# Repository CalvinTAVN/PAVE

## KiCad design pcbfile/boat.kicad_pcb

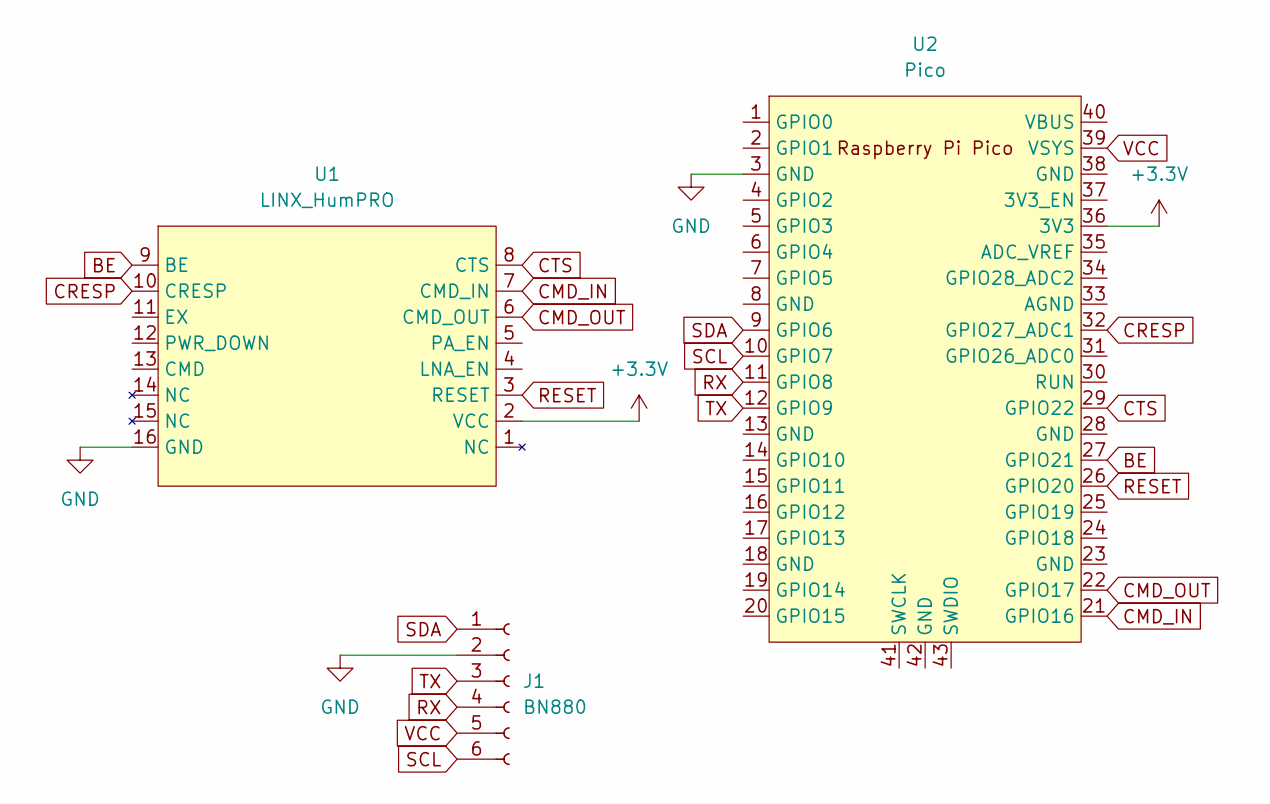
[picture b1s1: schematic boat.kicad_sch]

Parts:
J1: BN880; PinSocket_1x06_P2.54mm_Vertical
U1: LINX_HumPRO; Linx_HumPRO
U2: Pico; RPi_Pico_SMD_TH

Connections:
+3.3V: U1.2 (VCC), U2.36 (3V3)
BE: U1.9 (BE), U2.27 (GPIO21)
CMD_IN: U1.7 (CMD_IN), U2.21 (GPIO16)
CMD_OUT: U1.6 (CMD_OUT), U2.22 (GPIO17)
CRESP: U1.10 (CRESP), U2.32 (GPIO27_ADC1)
CTS: U1.8 (CTS), U2.29 (GPIO22)
GND: J1.2, U1.16 (GND), U2.3 (GND)
RESET: U1.3 (RESET), U2.26 (GPIO20)
RX: J1.4, U2.11 (GPIO8)
SCL: J1.6, U2.10 (GPIO7)
SDA: J1.1, U2.9 (GPIO6)
TX: J1.3, U2.12 (GPIO9)
VCC: J1.5, U2.39 (VSYS)

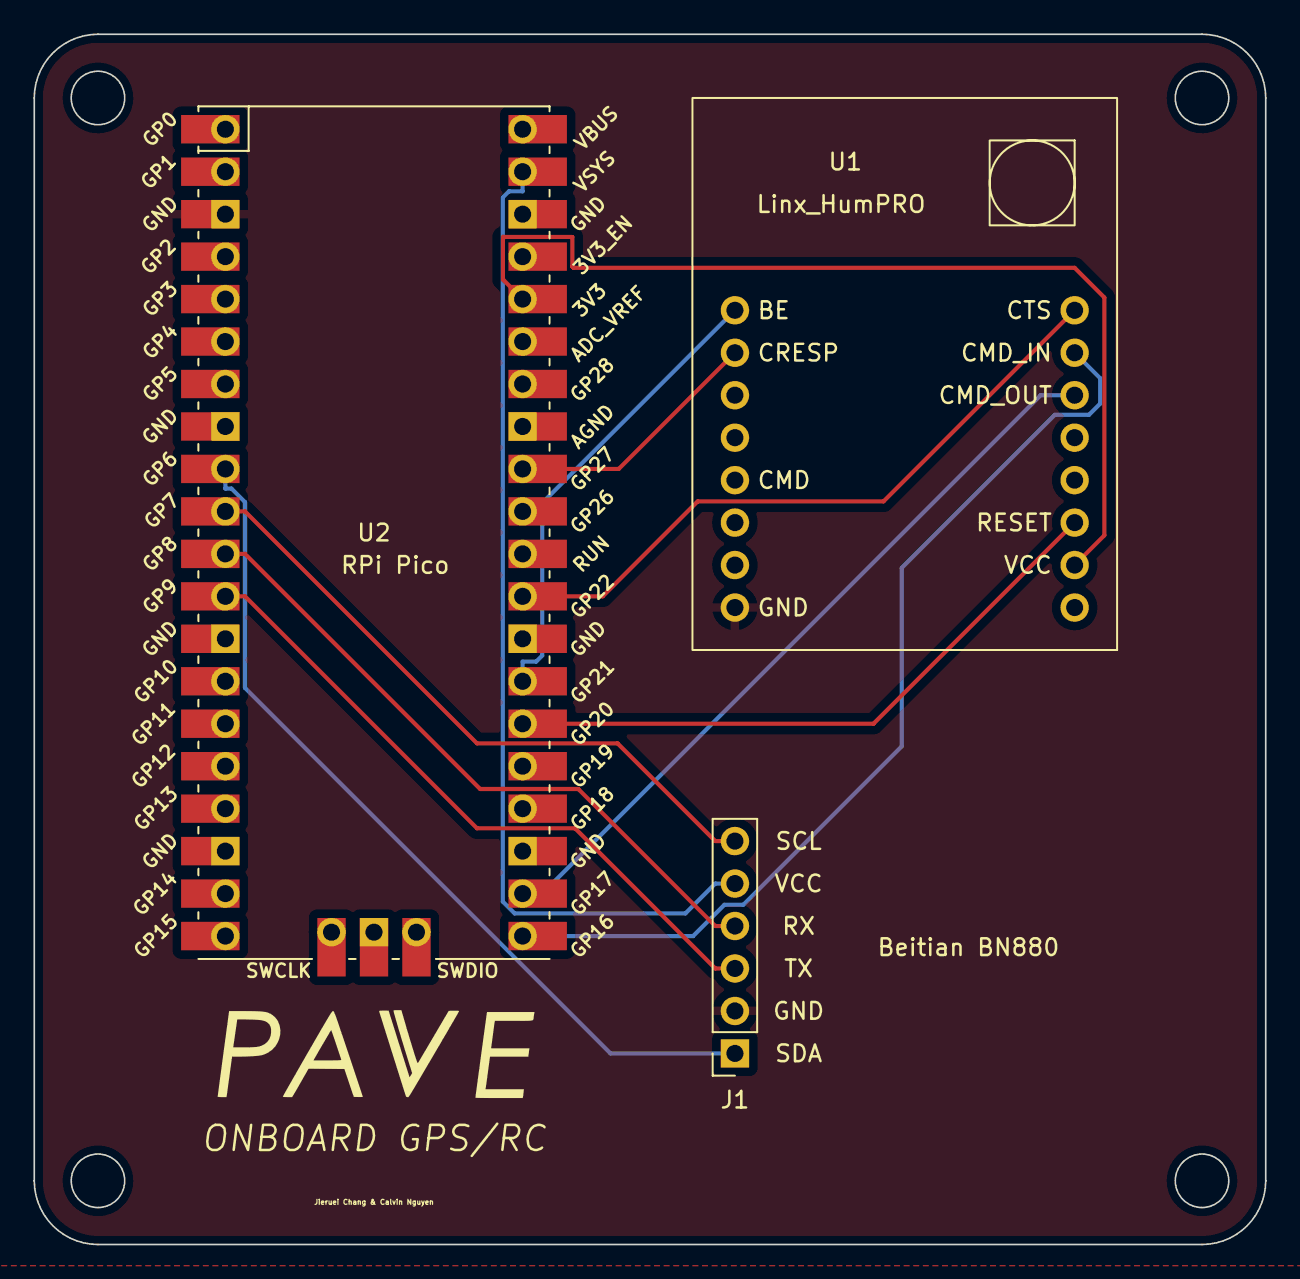
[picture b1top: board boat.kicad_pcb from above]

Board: 2 copper layers, 73.7 x 72.4 mm, 3 parts (0 on the bottom side), 13 nets.

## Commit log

2024-04-07 here
